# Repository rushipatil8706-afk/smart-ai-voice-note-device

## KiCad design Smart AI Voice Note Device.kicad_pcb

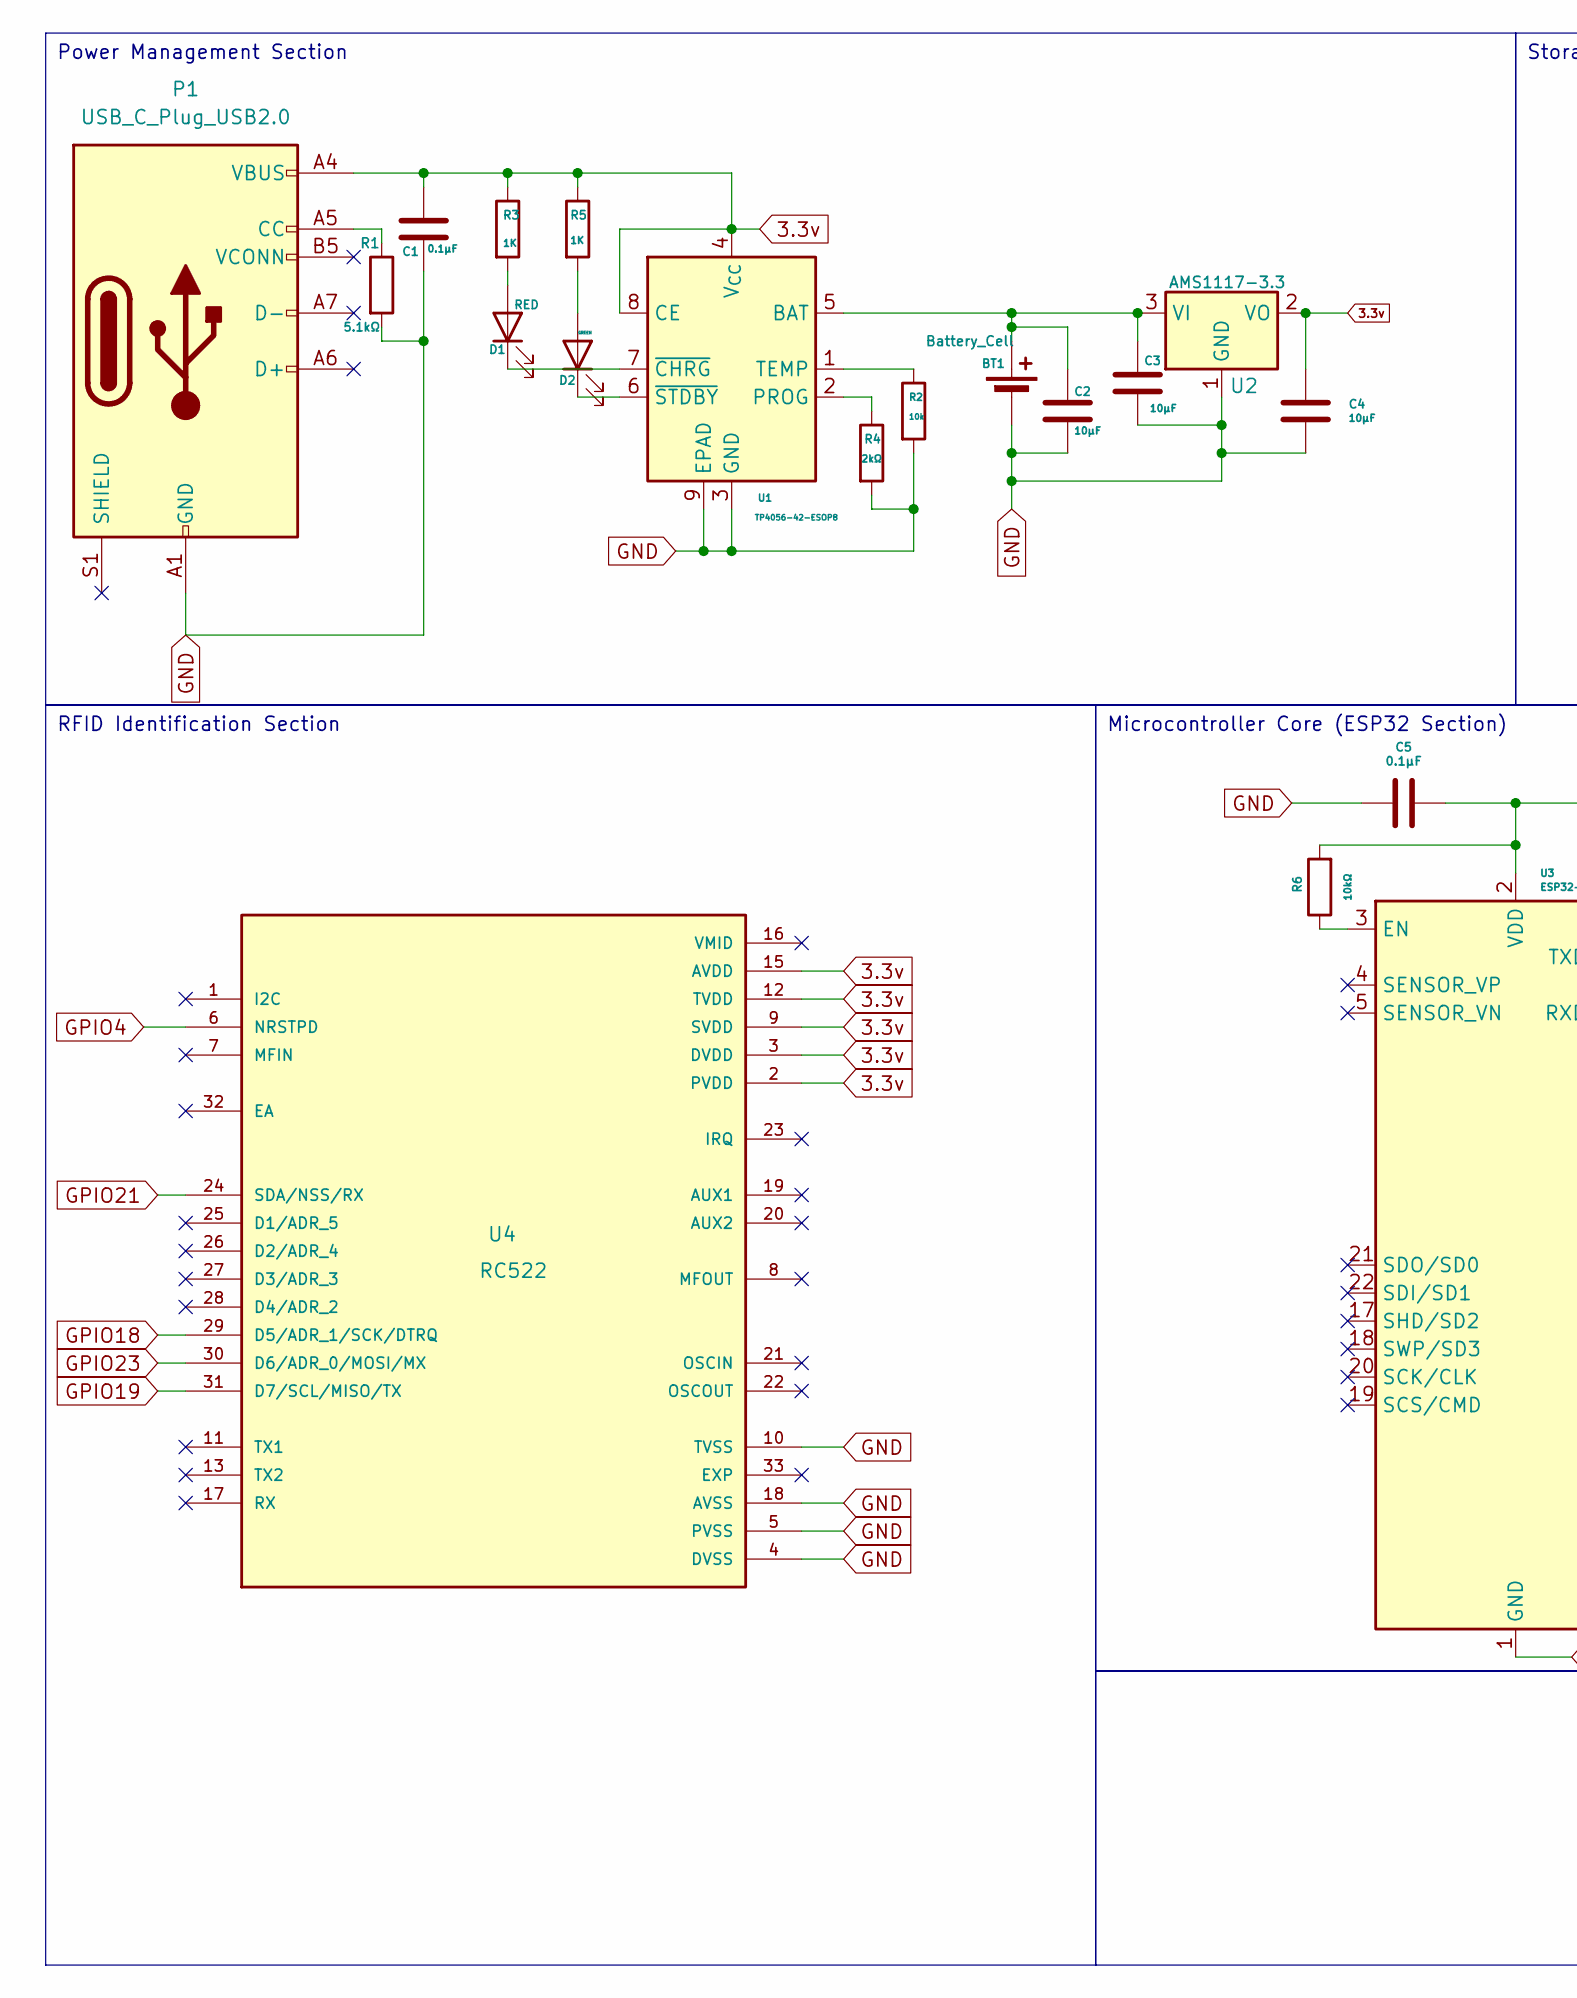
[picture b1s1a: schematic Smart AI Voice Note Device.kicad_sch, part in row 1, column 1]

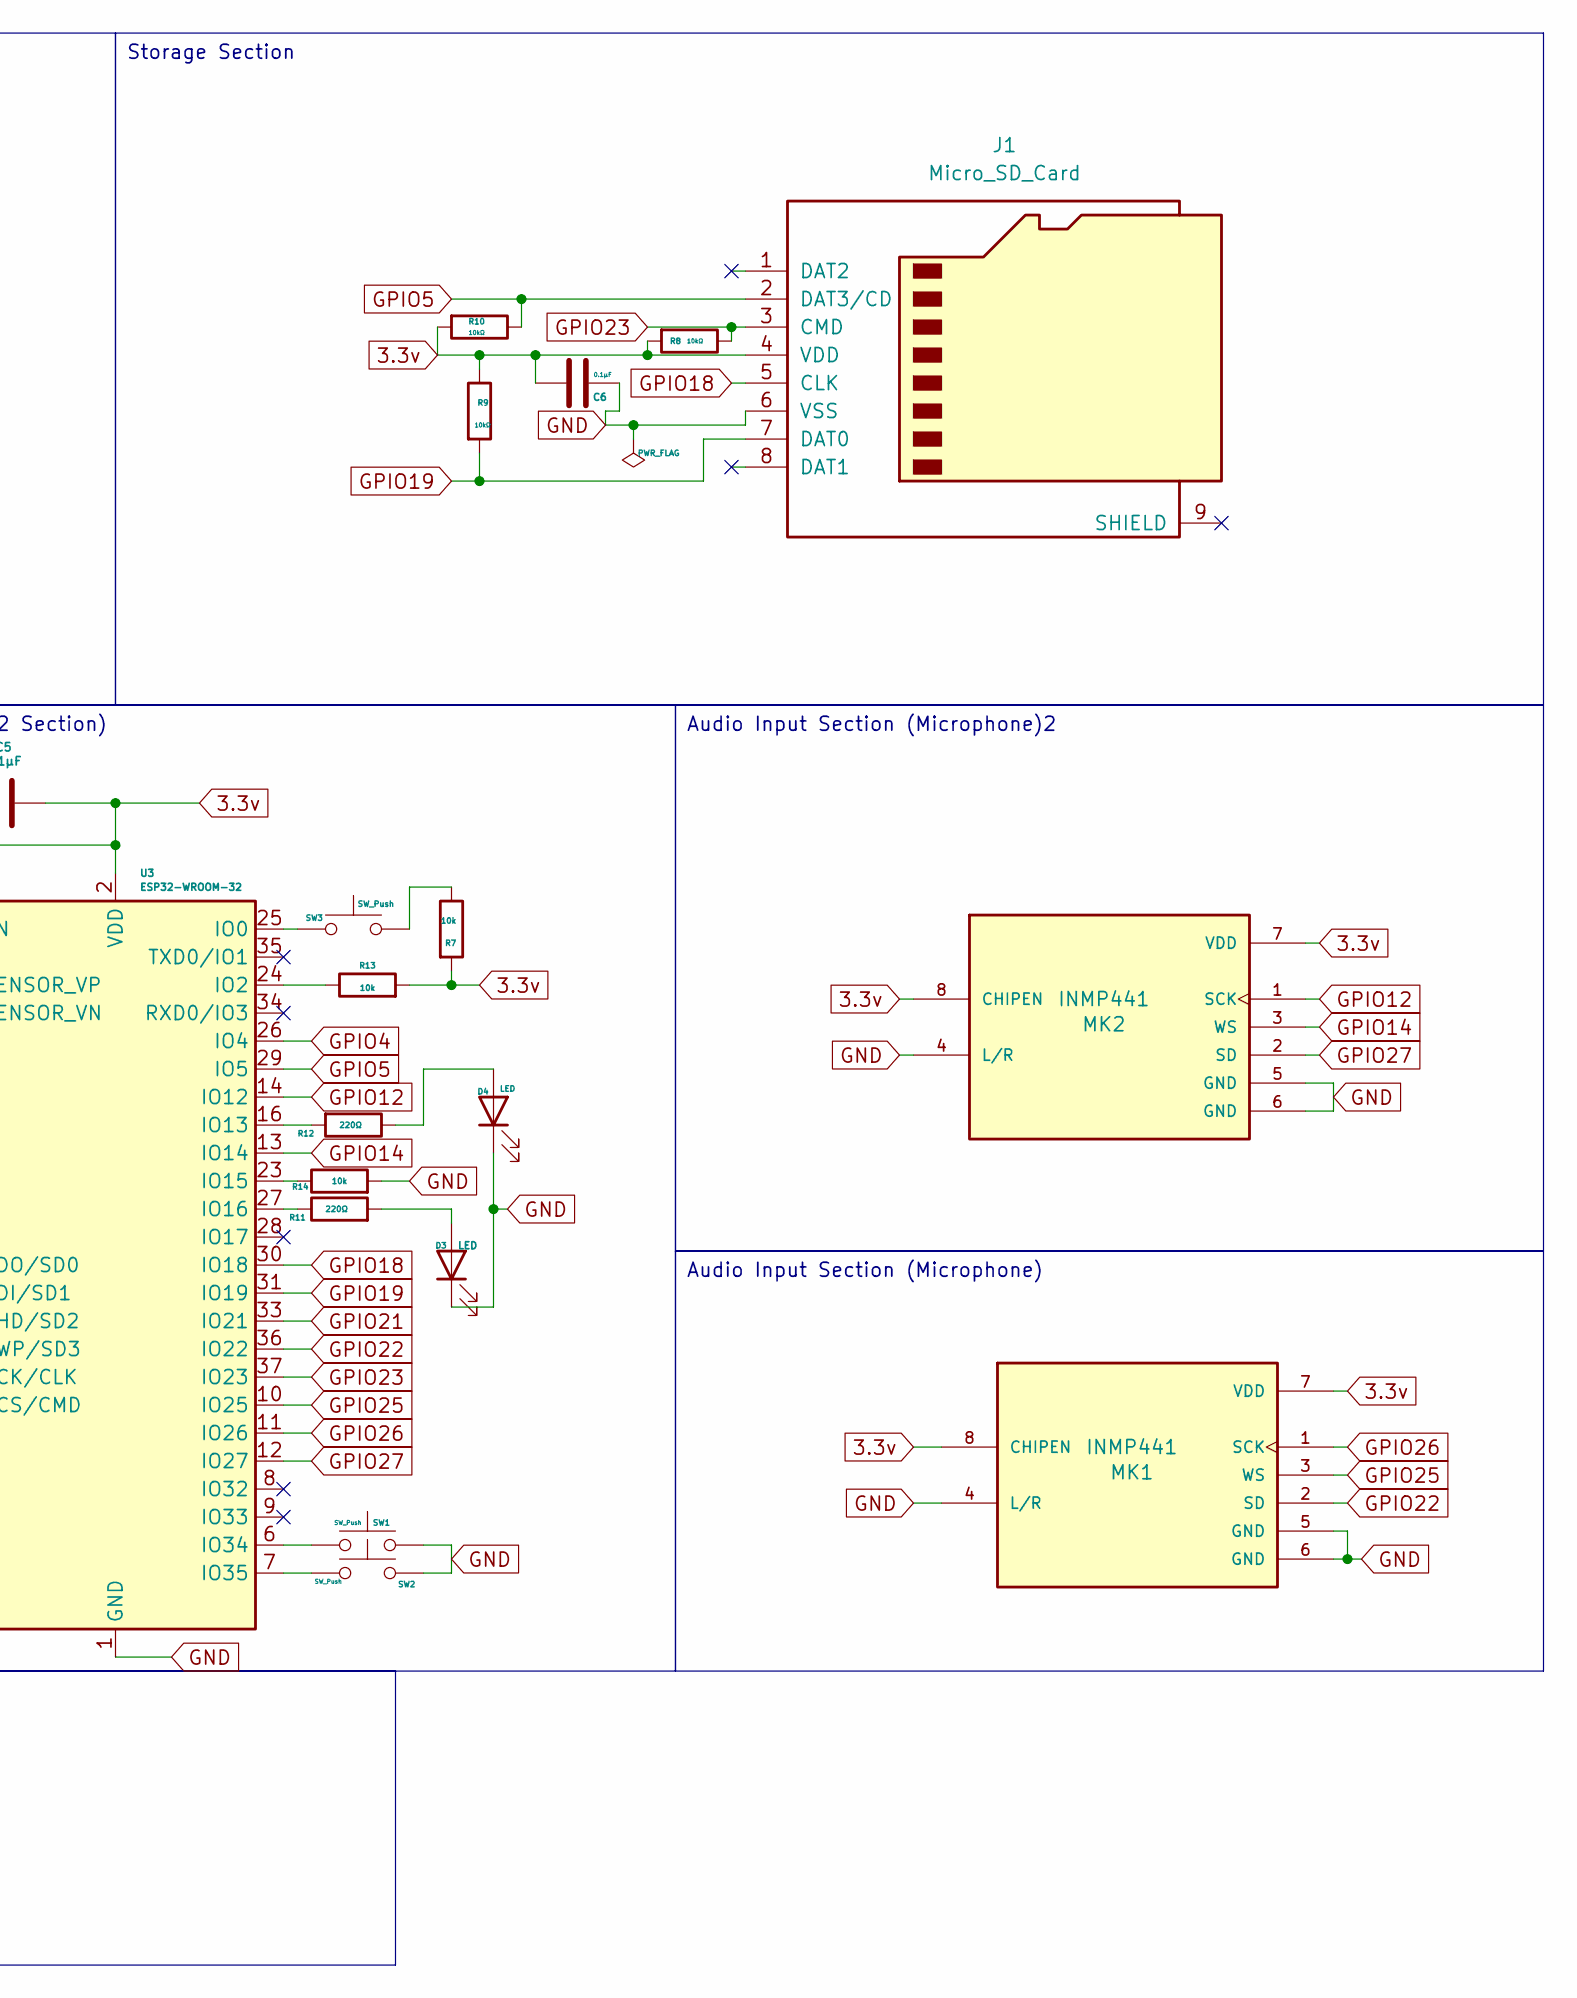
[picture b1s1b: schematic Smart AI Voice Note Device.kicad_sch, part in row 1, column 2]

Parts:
BT1: Battery_Cell; PinHeader_1x02_P2.54mm_Vertical
C1, C5, C6: 0.1µF; C_0603_1608Metric
C2, C3, C4: 10µF; C_0805_2012Metric
D1: RED; LED_0603_1608Metric
D2: GREEN; LED_0603_1608Metric
D3, D4: LED; LED_0603_1608Metric
J1: Micro_SD_Card; microSD_HC_Molex_47219-2001
MK1, MK2: INMP441; PinHeader_1x08_P2.54mm_Vertical; PARTREV 1.1
P1: USB_C_Plug_USB2.0; USB_C_Receptacle_GCT_USB4085
R1: 5.1kΩ; R_0603_1608Metric
R2, R7, R13, R14: 10k; R_0603_1608Metric
R3, R5: 1K; R_0603_1608Metric
R4: 2kΩ; R_0603_1608Metric
R6, R8, R9, R10: 10kΩ; R_0603_1608Metric
R11, R12: 220Ω; R_0603_1608Metric
SW1, SW2, SW3: SW_Push; SW_PUSH_6mm
U1: TP4056-42-ESOP8; SOIC-8-1EP_3.9x4.9mm_P1.27mm_EP2.41x3.3mm_ThermalVias
U2: AMS1117-3.3; SOT-223-3_TabPin2
U3: ESP32-WROOM-32
U4: RC522; HVQFN-32-1EP_5x5mm_P0.5mm_EP3.1x3.1mm; PARTREV 3.9

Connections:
3.3v: C1.1, C4.1, C5.2, C6.1, J1.4 (VDD), MK1.7 (VDD), MK1.8 (CHIPEN), MK2.7 (VDD), MK2.8 (CHIPEN), P1.A4 (VBUS), P1.A9 (VBUS), P1.B4 (VBUS), P1.B9 (VBUS), R3.1, R5.1, R6.2, R7.2, R8.2, R9.1, R10.2, R13.2, U1.4 (V_{CC}), U1.8 (CE), U2.2 (VO), U3.2 (VDD), U4.2 (PVDD), U4.3 (DVDD), U4.9 (SVDD), U4.12 (TVDD), U4.15 (AVDD)
GND: BT1.2 (-), C1.2, C2.2, C3.2, C4.2, C5.1, C6.2, D3.1 (K), D4.1 (K), J1.6 (VSS), MK1.4 (L/R), MK1.5 (GND), MK1.6 (GND), MK2.4 (L/R), MK2.5 (GND), MK2.6 (GND), P1.A1 (GND), P1.A12 (GND), P1.B1 (GND), P1.B12 (GND), R1.2, R2.2, R4.2, R14.2, SW1.2, SW2.2, U1.3 (GND), U1.9 (EPAD), U2.1 (GND), U3.1 (GND), U3.15 (GND), U3.38 (GND), U3.39 (GND), U4.4 (DVSS), U4.5 (PVSS), U4.10 (TVSS), U4.14 (TVSS), U4.18 (AVSS)
GPIO4: U3.26 (IO4), U4.6 (NRSTPD)
GPIO5: J1.2 (DAT3/CD), R10.1, U3.29 (IO5)
GPIO12: MK2.1 (SCK), U3.14 (IO12)
GPIO14: MK2.3 (WS), U3.13 (IO14)
GPIO18: J1.5 (CLK), U3.30 (IO18), U4.29 (D5/ADR_1/SCK/DTRQ)
GPIO19: J1.7 (DAT0), R9.2, U3.31 (IO19), U4.31 (D7/SCL/MISO/TX)
GPIO21: U3.33 (IO21), U4.24 (SDA/NSS/RX)
GPIO22: MK1.2 (SD), U3.36 (IO22)
GPIO23: J1.3 (CMD), R8.1, U3.37 (IO23), U4.30 (D6/ADR_0/MOSI/MX)
GPIO25: MK1.3 (WS), U3.10 (IO25)
GPIO26: MK1.1 (SCK), U3.11 (IO26)
GPIO27: MK2.2 (SD), U3.12 (IO27)
unnamed: BT1.1 (+), C2.1, C3.1, U1.5 (BAT), U2.3 (VI)
unnamed: D1.2 (A), R3.2
unnamed: D1.1 (K), U1.7 (~CHRG)
unnamed: D2.2 (A), R5.2
unnamed: D2.1 (K), U1.6 (~STDBY)
unnamed: D3.2 (A), R11.2
unnamed: D4.2 (A), R12.1
unnamed: P1.A5 (CC), R1.1
unnamed: R7.1, SW3.2
unnamed: R4.1, U1.2 (PROG)
unnamed: R2.1, U1.1 (TEMP)
unnamed: R6.1, U3.3 (EN)
unnamed: SW3.1, U3.25 (IO0)
unnamed: R13.1, U3.24 (IO2)
unnamed: R12.2, U3.16 (IO13)
unnamed: R14.1, U3.23 (IO15)
unnamed: R11.1, U3.27 (IO16)
unnamed: SW1.1, U3.6 (IO34)
unnamed: SW2.1, U3.7 (IO35)

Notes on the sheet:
Audio Input Section (Microphone)2
RFID Identification Section
Microcontroller Core (ESP32 Section)
Storage Section
Audio Input Section (Microphone)
Power Management Section

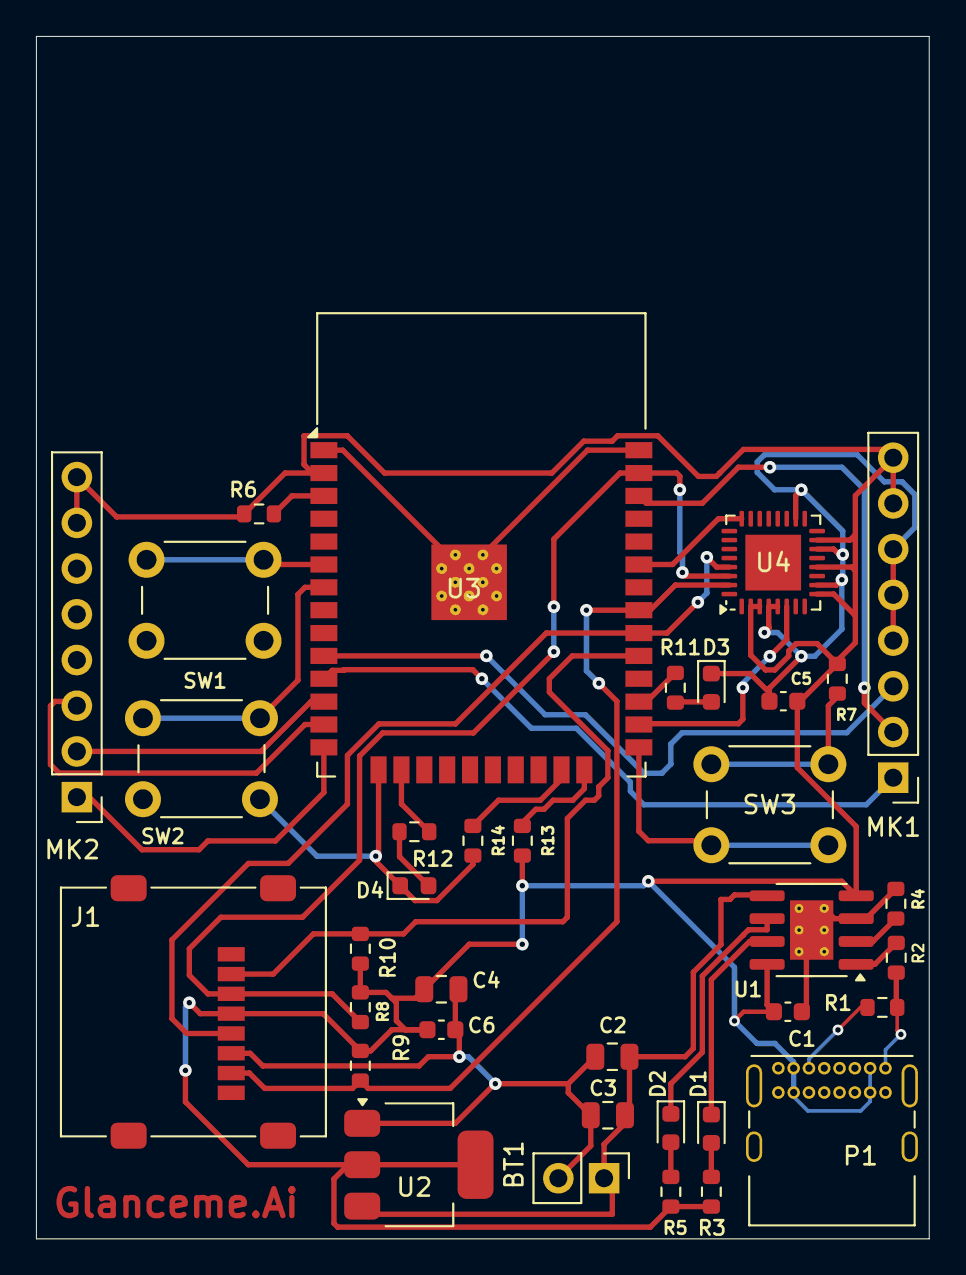
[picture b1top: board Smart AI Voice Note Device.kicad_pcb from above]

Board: 2 copper layers, 49.6 x 66.8 mm, 36 parts (0 on the bottom side), 33 nets.

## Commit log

2026-04-02 Gerber
2026-04-02 KiCad
2026-04-02 library
2026-04-02 datasheet
